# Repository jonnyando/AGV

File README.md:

# AGV

##Current Specs
- BLDC motor driver
- STM32F103C8 microcontroller
- LEDs on each phase's PWM output, so they will breath in sync with the speed of the motor
- Sense lines on all three phases, allowing sensorless operation
- UART connector
- SWD connector
- Vin up to 24V (need to double check voltage range on all parts)
- 3.3v linear reg (want to replace with switched)
- 3.3v rail indicator LED
- four quadrant operation (sw not yet implemented)

## TO DO
- add connection for rotary encoder
- add silkscreen indication for power input
- add bulk input capacitance
- get overall size down a little
- determine if parallel 'FETs are necessary for desired use cases.
- determine power handling capability (similar to above)

- usb port? depends on uC. Would need isolation probably
- isolated uart/i2c/spi port, for receiving commands from master/host
- add adc?

## Fixes:
- add power led on VBUS
- add led to EN_GATE pin to tell state
- increase drill size on stitching vias (currently unnecessarily small)
- fix/remove thermal relief on source pads for left most FETs
- add method to sense line voltages on each output phase, for back EMF sensing
- add fourth mounting hole
- increase package size where applicable (0402s are unnecessarily small in some places)
- do the capacitors on the back need to be there? maybe align them better at least
- improve fill polygon around C5 and C6
- align power leds more appropriately

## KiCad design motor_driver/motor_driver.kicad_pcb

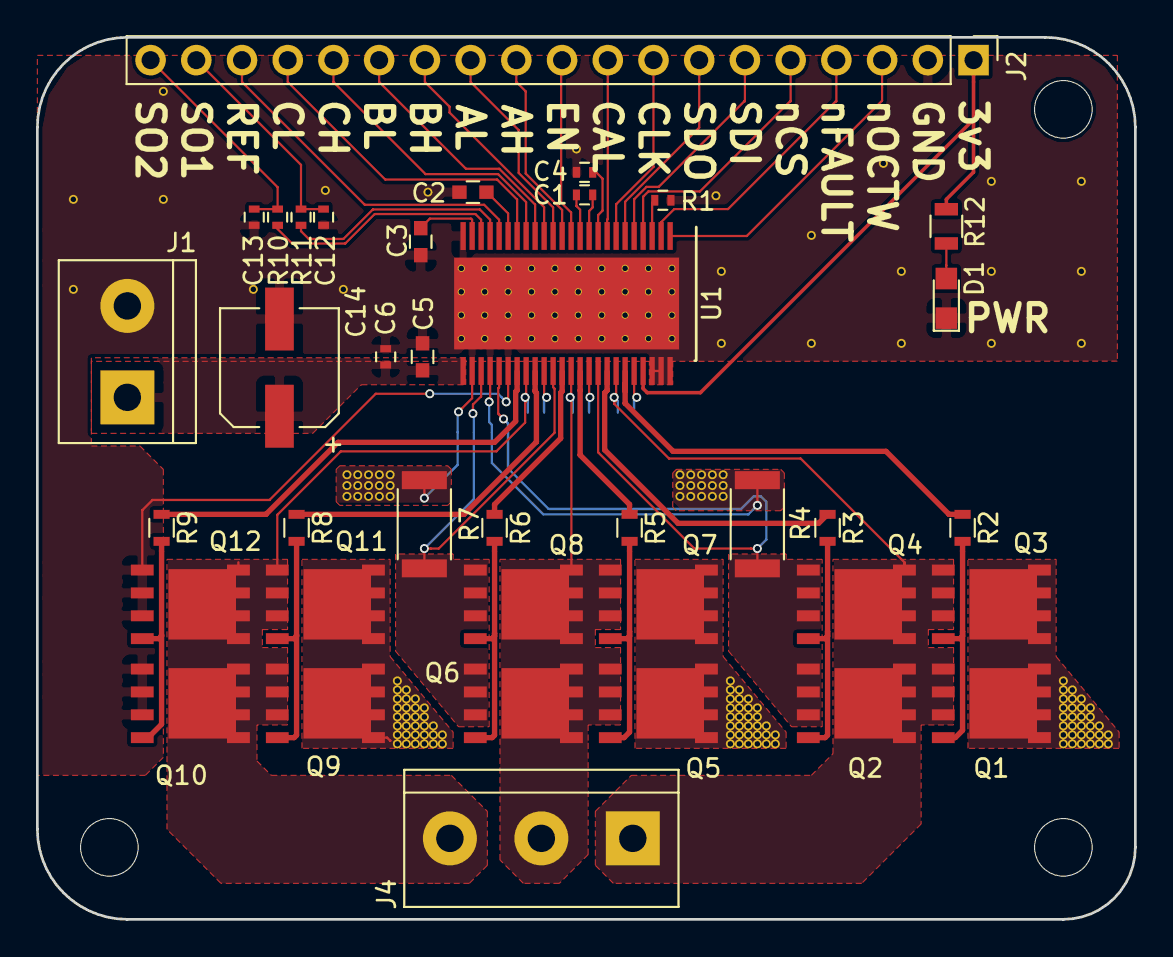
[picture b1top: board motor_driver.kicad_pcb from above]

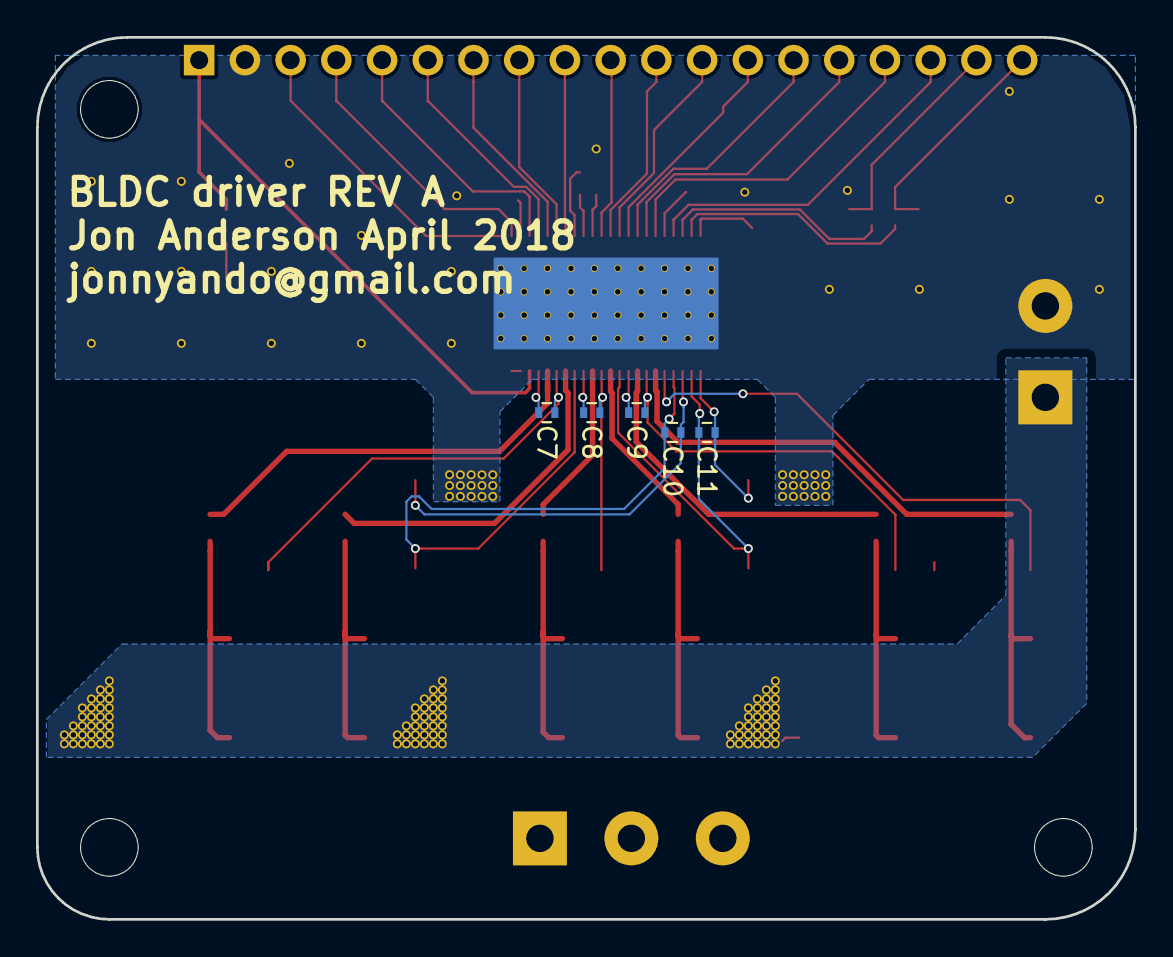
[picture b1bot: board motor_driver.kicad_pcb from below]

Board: 2 copper layers, 61.0 x 49.0 mm, 43 parts (5 on the bottom side), 49 nets.

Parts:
C1: 0.022uF; R_0402
C2, C3: 1uF; C_0603
C4: 2.2uF; R_0402
C5: 4.7uF; C_0603
C6, C7, C8, C9, C10, C11: 0.1uF; R_0402
C12, C13: C; R_0402
C14: CP1; CP_Elec_6.3x7.7
D1: LED; LED_0805
J1: Power_in; TerminalBlock_bornier-2_P5.08mm
J2: Conn_01x19; Pin_Header_Straight_1x19_Pitch2.54mm
J4: Screw_Terminal_01x03; TerminalBlock_bornier-3_P5.08mm
Q1, Q2, Q3, Q4, Q5, Q6, Q7, Q8, Q9, Q10, Q11, Q12: N_MOSFET; PQFN8_5x6
R1: 0R; R_0402
R2, R3, R5, R6, R8, R9: 10R; R_0603
R4, R7: 0.01R; R_2010
R10, R11: 56R; R_0402
R12: 1KR; R_0805
U1: DRV8303; HTSSOP-48-_Pitch0.5mm

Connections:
+3V3: J2.1, R12.2, U1.45
/AH: J2.11, U1.13
/AL: J2.12, U1.14
/BH: J2.13, U1.15
/BL: J2.14, U1.16
/CH: J2.15, U1.17
/CL: J2.16, U1.18
/DC_CAL: J2.9, U1.8
/EN_GATE: J2.10, U1.12
/GH_A: R2.1, U1.43
/GH_B: R5.1, U1.38
/GH_C: R8.1, U1.33
/GL_A: R3.1, U1.41
/GL_B: R6.1, U1.36
/GL_C: R9.1, U1.31
/REF: J2.17, U1.20
/SCLK: J2.8, U1.7
/SDI: J2.6, U1.5
/SDO: J2.7, U1.6
/SH_A: C7.1, J4.1, Q1.3, Q2.2, Q3.3, Q4.2, U1.42
/SH_B: C8.1, J4.2, Q5.3, Q6.2, Q7.3, Q8.2, U1.37
/SH_C: C9.1, J4.3, Q9.3, Q10.2, Q11.3, Q12.2, U1.32
/SL_A: C10.2, Q2.3, Q4.3, R4.1, U1.29, U1.40
/SL_B: C11.2, Q6.3, Q8.3, R7.1, U1.27, U1.35
/SO1: C12.2, J2.18, R11.1
/SO2: C13.2, J2.19, R10.1
/nCS: J2.5, U1.4
/nFAULT: J2.4, U1.2
/nOCTW: J2.3, U1.1
GND: C2.2, C3.2, C4.2, C5.2, C6.2, C10.1, C11.1, C12.1, C13.1, C14.2, D1.1, J1.2, J2.2, Q10.3, Q12.3, R1.1, R4.2, R7.2, U1.24, U1.26, U1.28, U1.30, U1.46, U1.47, U1.48, U1.GND
unnamed: C1.1, U1.10
unnamed: C1.2, U1.11
unnamed: C2.1, U1.19
unnamed: C3.1, U1.23
unnamed: C4.1, U1.9
unnamed: C7.2, U1.44
unnamed: C8.2, U1.39
unnamed: C9.2, U1.34
unnamed: D1.2, R12.1
unnamed: Q1.1, Q3.1, R2.2
unnamed: Q2.1, Q4.1, R3.2
unnamed: Q5.1, Q7.1, R5.2
unnamed: Q6.1, Q8.1, R6.2
unnamed: Q10.1, Q12.1, R9.2
unnamed: Q9.1, Q11.1, R8.2
unnamed: R1.2, U1.3
unnamed: R10.2, U1.22
unnamed: R11.2, U1.21
VBUS: C5.1, C6.1, C14.1, J1.1, Q1.2, Q3.2, Q5.2, Q7.2, Q9.2, Q11.2, U1.25

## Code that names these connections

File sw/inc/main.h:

#ifndef __MAIN_H__
#define __MAIN_H__

/* Includes ------------------------------------------------------------------*/

// #include "syscalls.h"
// #include "stm32f1xx_hal.h"
#ifndef STM32F103xB
    #define STM32F103xB
#endif
#include "stm32f1xx.h"
#include "spi.h"
#include "uart.h"
#include "gpio.h"
#include "tim.h"
#include <stdio.h>
#include <math.h>
#include "drv8303.h"
#include "adc.h"
#include "dma.h"
#include "iwdg.h"

/* Private define ------------------------------------------------------------*/
#define PI 3.14159265358979323846264


#define nOCTW_Pin       15 // A
#define nOCTW_Port      GPIOA
#define nFAULT_Pin      12 // B
#define nFAULT_Port     GPIOB
#define DC_CAL_Pin      12     // A 
#define DC_CAL_Port     GPIOA
#define EN_GATE_Pin     11     // A
#define EN_GATE_Port    GPIOA
#define INH_A_Pin       8      // A
#define INH_B_Pin       9      // A
#define INH_C_Pin       10     // A
#define INH_A_Port      GPIOA
#define INH_B_Port      GPIOA
#define INH_C_Port      GPIOA
#define INL_A_Pin       13     // B
#define INL_B_Pin       14     // B
#define INL_C_Pin       15     // B
#define INL_A_Port      GPIOB
#define INL_B_Port      GPIOB
#define INL_C_Port      GPIOB
#define LED_FAULT_Pin   11     // B
#define LED_FAULT_Port  GPIOB
#define ENC_I           8      // B
#define ENC_A           4      // B
#define ENC_B           5      // B
#define ASENSE_Pin      1      // A
#define BSENSE_Pin      2      // A
#define CSENSE_Pin      3      // A
#define ASENSE_Port     GPIOA
#define BSENSE_Port     GPIOA
#define CSENSE_Port     GPIOA
#define SO1_Pin         1      // B
#define SO2_Pin         0      // B
#define SO1_Port        GPIOB
#define SO2_Port        GPIOB
/* SPI Pins */
#define SPI_PORT        GPIOA
#define SPI_Pin_NSS     4
#define SPI_Pin_SCK     5
#define SPI_Pin_MISO    6
#define SPI_Pin_MOSI    7
/* USART1 Pins */
#define USART1_PORT     GPIOB
#define USART_Pin_TX    6
#define USART_Pin_RX    7


// #define B1_Pin GPIO_PIN_13
// #define B1_GPIO_Port GPIOC
// #define B1_EXTI_IRQn EXTI15_10_IRQn
// #define USART_TX_Pin GPIO_PIN_2
// #define USART_TX_GPIO_Port GPIOA
// #define USART_RX_Pin GPIO_PIN_3
// #define USART_RX_GPIO_Port GPIOA
// #define SWO_Pin GPIO_PIN_3
// #define SWO_GPIO_Port GPIOB



#endif /* __MAIN_H__ */

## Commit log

2018-03-30 migrated project to github
2018-04-04 Finished layout and generated gerbers
2018-05-08 Added TODO items to README.md
2018-06-03 moved hardware and software into discrete folders. Added software template
2018-06-03 updating
2018-06-03 trying to fix sw folder
2018-06-03 re-added sw folder
2018-06-03 began spi integration
2018-06-16 SPI is now working. Wrote a few debug functions using HAL_UART3
2018-06-16 readded _hap_spi.c after accidental removal
2018-06-17 Uart1-3, printf, spi all working
2018-11-02 re organised file structure, and updated hardware files with new Altium version
2018-11-11 update software
2018-11-11 blink PB11 on new hardware
2018-11-19 functioning SPI comms
2018-11-21 fixed grounding path to power input connector. fixed pin issue on AVDD in drv8303
2018-11-28 swapped TIM1_CHx to correct pins. Moved UART to alt pins, and swapped a few nets around to simplify routing. Gerbers of this commit submitted for fab
2018-11-28 began switch over to vscode
2018-11-28 renamed some UART functions
2018-11-28 removed supurfluous code
2018-11-28 updated .gitignore to remove altium history and __previews
2018-11-28 updated _error_handler()
2018-11-29 created drv_write() and set a reg for 3-PWM mode control
2018-11-29 changed casing on src & inc folders
2018-12-15 updated pdf
2018-12-15 minor main changes (sorry for the shit commit)
2019-01-29 begun modifications for Rev C - currently unworking state
2019-02-02 added SMPS and flyback diode
2019-02-03 Added encoder connetions and reworked connectors
2019-02-08 updated power schematic
2019-02-09 reworked gpio manipulation and changed name of uart lib
2019-02-09 tidid up main.c commented lines
2019-02-09 begun removal of HAL
2019-02-09 more tidying of superfluous cmsis/hal garbage
2019-02-15 updated PCB for new revision. Gerbers ordered
2019-05-19 SPI working for real
2019-07-07 HAL is gone! cleanup todo
2019-07-13 removed HAL
2019-07-13 hw files
2019-07-17 cleaned up pin assignment in uart driver
2019-07-17 changed default GPIO AF speed to 50MHz
2019-09-03 updated launch file to use ST-Link V2-1
2019-09-03 updated drv driver to use an object handle
2019-09-03 uart driver now peripheral number agnostic
2019-09-03 cleaned up spi driver
2019-09-03 simplified init code. Simplified overall file
2019-10-13 interrupts for debugging. WIP
2019-10-17 work commit
